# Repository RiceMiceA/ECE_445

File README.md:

# NuChef<sup>TM</sup> - AI Culinary Assistant

## Table of Contents
1. [Final Product](#1-final-product)
    - [Photos](#photos)
    - [YouTube Demo](#youtube-demo)
2. [How to use our repo?](#2-how-to-use-our-repo)
    - [Init](#21-init)
    - [Managing the submodule Unity folder](#22-managing-the-submodule-unity-folder)
    - [Network Configuration](#3-network-configuration)
    - [Troubleshooting](#4-troubleshooting)
5. [Third-Party Libraries & Licenses](#5-third-party-libraries--licenses)

## 1. Final Product
### Photos

### YouTube Demo

## 2. How to use our repo?

### 2.1 Init
#### Freshly Clone 1st time
```bash
git clone --recurse-submodules <repo-url>
```

This does everything:
- clones the parent repo
- initializes submodules
- checks out the correct commits

#### Already cloned repo
```bash
git submodule update --init --recursive
```

### 2.2 Managing the submodule Unity folder
#### 2.2.1 Before Work/Update
#### In parent folder
```bash
git pull
git submodule update --init --recursive
```

#### 2.2.2 Post-work
```bash
cd path/to/submodule
git checkout main
git pull origin main
git add .
git commit -m "Update submodule"
git push origin main

cd /path/to/parent-repo
git add Software/src/Unity-PassthroughCameraApiSamples
git commit -m "Bump submodule"
git push origin main
```

### Verify Health
```bash
git submodule status
```

### Tip
```bash
git config --global submodule.recurse true
# if we wanna track the specific branch
git submodule set-branch --branch tony Software/src/Unity-PassthroughCameraApiSamples
git submodule update --remote
```

## 3. Network Configuration

### Kill previous run
```bash
kill $(lsof -t -i:8000) 
```

### Update IP Address before operation
```bash
Check the current ip address: 
```
When switching networks, update the backend IP (`192.168.x.x`) in these files:

| File                                                                                                                                                                                                                                                                                                       | Line | Variable      |
| ---------------------------------------------------------------------------------------------------------------------------------------------------------------------------------------------------------------------------------------------------------------------------------------------------------- | ---- | ------------- |
| [`Software/src/Unity-PassthroughCameraApiSamples/Assets/PassthroughCameraApiSamples/MultiObjectDetection/DetectionManager/Scripts/BackendClient.cs`](Software/src/Unity-PassthroughCameraApiSamples/Assets/PassthroughCameraApiSamples/MultiObjectDetection/DetectionManager/Scripts/BackendClient.cs#L19) | 19   | `m_baseUrl`   |
| [`Software/src/web_app/main/script.js`](Software/src/web_app/main/script.js#L6)                                                                                                                                                                                                                            | 6    | `BACKEND_URL` |

> **Note:** The ESP32 now communicates via **BLE** (not WiFi), so it no longer needs an IP address or network config.

Then start the backend and BLE bridge:
```bash
# Terminal 1 — backend
cd Software/src/web_app
source .env   # loads OPENAI_API_KEY, OPENAI_MODEL, USE_LLM_PLANNER from .env file
uvicorn backend:app --host 0.0.0.0 --port 8000 --reload

# Terminal 2 — BLE bridge (connects to ESP32 over Bluetooth, forwards to backend)
pip install bleak httpx   # first time only
python ble_bridge.py
```

## 4. Troubleshooting

### Upload new ESP32 file
```bash
~/.platformio/penv/bin/pio run 2>&1 | tail -20
```

### ESP32 BLE not broadcasting / bridge can't find device
1. **Press the physical RESET button** on the ESP32-S3 board. It will re-advertise as `NuChef-Dispenser` within a few seconds.
2. If the bridge still can't find it, kill and restart `ble_bridge.py`. Linux's BlueZ stack sometimes caches stale BLE data.
3. As a last resort, power-cycle the ESP32 (unplug & replug USB).

### Serial port changed (`/dev/ttyACM0` ↔ `/dev/ttyACM1`)
After a reset or replug the port may shift. Check with:
```bash
ls /dev/ttyACM*
```
Then update `upload_port` and `monitor_port` in `Software/src/esp_driver/platformio.ini` if you need to re-flash.

### Permission denied on `/dev/ttyACM*`
```bash
sudo usermod -aG dialout $USER
# then log out & back in (or reboot) for the group to take effect
```

### Bridge connects but dispense doesn't trigger from the UI
- Make sure the backend (`uvicorn`) **and** `ble_bridge.py` are both running.
- Verify `BACKEND_URL` in `script.js` is `window.location.origin` (not a hardcoded IP).
- Check the bridge terminal for `BLE CMD →` and `write OK` logs when you click **Dispense**.

### Quick sanity check (motor spin from CLI)
```bash
# Direct BLE test — bypasses the backend entirely
python3 -c "
import asyncio
from bleak import BleakClient, BleakScanner
SVC  = '4e7a9b1c-d203-4e2a-b8f1-67c1d9e3f5a0'
CMD  = '4e7a9b1c-d203-4e2a-b8f1-67c1d9e3f5a1'
async def test():
    dev = await BleakScanner.find_device_by_name('NuChef-Dispenser', timeout=10)
    async with BleakClient(dev) as c:
        await c.write_gatt_char(CMD, b'spin', response=True)
        await asyncio.sleep(5)
        await c.write_gatt_char(CMD, b'stop', response=True)
asyncio.run(test())
"
```

## 5. Third-Party Libraries & Licenses

### Unity Utility Packages (MIT)
- **Repository:** https://github.com/meta-quest/Unity-UtilityPackages
- **Author:** Meta Platforms, Inc. and affiliates
- **License:** MIT License

> Meta Quest, "Unity-UtilityPackages," GitHub. [Online]. Available: https://github.com/meta-quest/Unity-UtilityPackages. [Accessed: May 7, 2026].

MIT License attribution:
```
Unity Utility Packages
Copyright (c) Meta Platforms, Inc. and affiliates.
Licensed under the MIT License.
https://github.com/meta-quest/Unity-UtilityPackages
```

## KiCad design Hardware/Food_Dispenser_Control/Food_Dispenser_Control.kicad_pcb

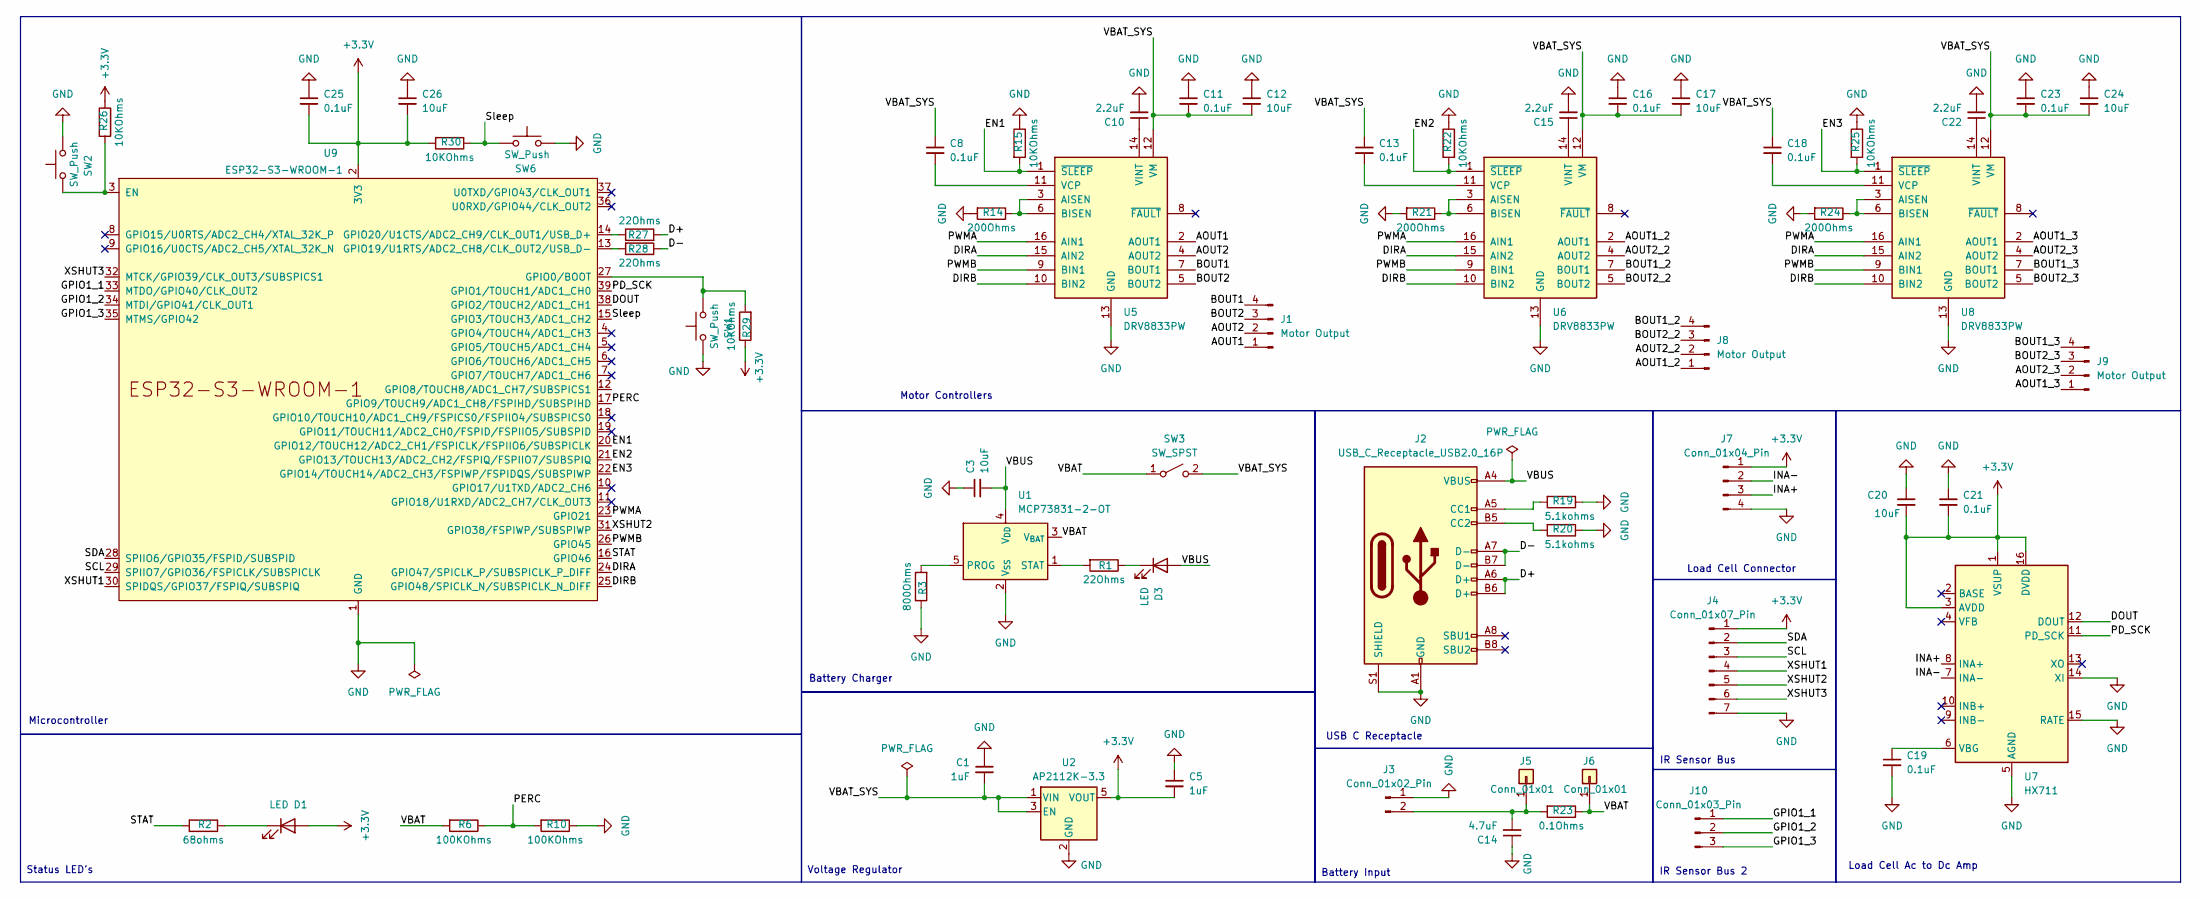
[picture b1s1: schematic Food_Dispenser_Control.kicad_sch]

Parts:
C1, C5: 1uF; C_0805_2012Metric_Pad1.18x1.45mm_HandSolder
C3, C12, C17, C20, C24, C26: 10uF; C_0805_2012Metric_Pad1.18x1.45mm_HandSolder
C8, C11, C13, C16, C18, C19, C21, C23, C25: 0.1uF; C_0805_2012Metric_Pad1.18x1.45mm_HandSolder
C10, C15, C22: 2.2uF; C_0805_2012Metric_Pad1.18x1.45mm_HandSolder
C14: 4.7uF; C_0805_2012Metric_Pad1.18x1.45mm_HandSolder
D1, D3: LED; LED_0805_2012Metric_Pad1.15x1.40mm_HandSolder
J1, J8, J9: Motor Output; TerminalBlock_Phoenix_MKDS-1,5-4_1x04_P5.00mm_Horizontal
J2: USB_C_Receptacle_USB2.0_16P; USB_C_Receptacle_GCT_USB4105-xx-A_16P_TopMnt_Horizontal
J3: Conn_01x02_Pin; TerminalBlock_Phoenix_MKDS-1,5-2_1x02_P5.00mm_Horizontal
J4: Conn_01x07_Pin; TerminalBlock_Phoenix_MKDS-1,5-7_1x07_P5.00mm_Horizontal
J5, J6: Conn_01x01; TestPoint_Pad_D1.5mm
J7: Conn_01x04_Pin; TerminalBlock_Phoenix_MKDS-1,5-4_1x04_P5.00mm_Horizontal
J10: Conn_01x03_Pin; TerminalBlock_Phoenix_MKDS-1,5-3_1x03_P5.00mm_Horizontal
R1, R27, R28: 22Ohms; R_0805_2012Metric_Pad1.20x1.40mm_HandSolder
R2: 68ohms; R_0805_2012Metric_Pad1.20x1.40mm_HandSolder
R3: 800Ohms; R_0805_2012Metric_Pad1.20x1.40mm_HandSolder
R6, R10: 100KOhms; R_0805_2012Metric_Pad1.20x1.40mm_HandSolder
R14, R21, R24: 200Ohms; R_0805_2012Metric_Pad1.20x1.40mm_HandSolder
R15, R22, R25, R26, R29, R30: 10KOhms; R_0805_2012Metric_Pad1.20x1.40mm_HandSolder
R19, R20: 5.1kohms; R_0805_2012Metric_Pad1.20x1.40mm_HandSolder
R23: 0.1Ohms; R_0805_2012Metric_Pad1.20x1.40mm_HandSolder
SW1, SW2, SW6: SW_Push; SW_PUSH_6mm_H5mm
SW3: SW_SPST; SW_DIP_SPSTx01_Slide_6.7x4.1mm_W7.62mm_P2.54mm_LowProfile
U1: MCP73831-2-OT; SOT-23-5
U2: AP2112K-3.3; SOT-23-5
U5, U6, U8: DRV8833PW; TSSOP-16_4.4x5mm_P0.65mm
U7: HX711; SOP-16_3.9x9.9mm_P1.27mm
U9: ESP32-S3-WROOM-1

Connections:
+3.3V: C5.2, C20.2, C21.2, C25.2, C26.2, D1.2 (A), J4.1, J7.1, R26.1, R29.1, R30.2, U2.5 (VOUT), U7.1 (VSUP), U7.3 (AVDD), U7.16 (DVDD), U9.2 (3V3)
/AOUT1: J1.1, U5.2 (AOUT1)
/AOUT1_2: J8.1, U6.2 (AOUT1)
/AOUT1_3: J9.1, U8.2 (AOUT1)
/AOUT2: J1.2, U5.4 (AOUT2)
/AOUT2_2: J8.2, U6.4 (AOUT2)
/AOUT2_3: J9.2, U8.4 (AOUT2)
/BOUT1: J1.4, U5.7 (BOUT1)
/BOUT1_2: J8.4, U6.7 (BOUT1)
/BOUT1_3: J9.4, U8.7 (BOUT1)
/BOUT2: J1.3, U5.5 (BOUT2)
/BOUT2_2: J8.3, U6.5 (BOUT2)
/BOUT2_3: J9.3, U8.5 (BOUT2)
/D+: J2.A6 (D+), J2.B6 (D+), R27.2
/D-: J2.A7 (D-), J2.B7 (D-), R28.1
/DIRA: U5.15 (AIN2), U6.15 (AIN2), U8.15 (AIN2), U9.24 (GPIO47/SPICLK_P/SUBSPICLK_P_DIFF)
/DIRB: U5.10 (BIN2), U6.10 (BIN2), U8.10 (BIN2), U9.25 (GPIO48/SPICLK_N/SUBSPICLK_N_DIFF)
/DOUT: U7.12 (DOUT), U9.38 (GPIO2/TOUCH2/ADC1_CH1)
/EN1: R15.2, U5.1 (~SLEEP), U9.20 (GPIO12/TOUCH12/ADC2_CH1/FSPICLK/FSPIIO6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)
/EN2: R22.2, U6.1 (~SLEEP), U9.21 (GPIO13/TOUCH13/ADC2_CH2/FSPIQ/FSPIIO7/S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)
/EN3: R25.2, U8.1 (~SLEEP), U9.22 (GPIO14/TOUCH14/ADC2_CH3/FSPIWP/FSPIDQS/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)
/GPIO1_1: J10.1, U9.33 (MTDO/GPIO40/CLK_OUT2)
/GPIO1_2: J10.2, U9.34 (MTDI/GPIO41/CLK_OUT1)
/GPIO1_3: J10.3, U9.35 (MTMS/GPIO42)
/INA+: J7.3, U7.8 (INA+)
/INA-: J7.2, U7.7 (INA-)
/PD_SCK: U7.11 (PD_SCK), U9.39 (GPIO1/TOUCH1/ADC1_CH0)
/PERC: R6.1, R10.2, U9.17 (GPIO9/TOUCH9/ADC1_CH8/FSPIHD/SUBSPIHD)
/PWMA: U5.16 (AIN1), U6.16 (AIN1), U8.16 (AIN1), U9.23 (GPIO21)
/PWMB: U5.9 (BIN1), U6.9 (BIN1), U8.9 (BIN1), U9.26 (GPIO45)
/SCL: J4.3, U9.29 (SPIIO7/GPIO36/FSPICLK/SUBSPICLK)
/SDA: J4.2, U9.28 (SPIIO6/GPIO35/FSPID/SUBSPID)
/STAT: R2.2, U9.16 (GPIO46)
/Sleep: R30.1, SW6.1, U9.15 (GPIO3/TOUCH3/ADC1_CH2)
/VBAT: J6.1, R6.2, R23.1, SW3.1 (A), U1.3 (V_{BAT})
/VBAT_SYS: C1.2, C8.1, C11.2, C12.2, C13.1, C16.2, C17.2, C18.1, C23.2, C24.2, SW3.2 (B), U2.1 (VIN), U2.3 (EN), U5.12 (VM), U6.12 (VM), U8.12 (VM)
/VBUS: C3.2, D3.2 (A), J2.A4 (VBUS), J2.A9 (VBUS), J2.B4 (VBUS), J2.B9 (VBUS), U1.4 (V_{DD})
/XSHUT1: J4.4, U9.30 (SPIDQS/GPIO37/FSPIQ/SUBSPIQ)
/XSHUT2: J4.5, U9.31 (GPIO38/FSPIWP/SUBSPIWP)
/XSHUT3: J4.6, U9.32 (MTCK/GPIO39/CLK_OUT3/SUBSPICS1)
GND: C1.1, C3.1, C5.1, C10.2, C11.1, C12.1, C14.1, C15.2, C16.1, C17.1, C19.2, C20.1, C21.1, C22.2, C23.1, C24.1, C25.1, C26.1, J2.A1 (GND), J2.A12 (GND), J2.B1 (GND), J2.B12 (GND), J2.S1 (SHIELD), J3.1, J4.7, J7.4, R3.1, R10.1, R14.2, R15.1, R19.1, R20.1, R21.2, R22.1, R24.2, R25.1, SW1.1, SW2.2, SW6.2, U1.2 (V_{SS}), U2.2 (GND), U5.13 (GND), U6.13 (GND), U7.5 (AGND), U7.14 (XI), U7.15 (RATE), U8.13 (GND), U9.1 (GND), U9.40 (GND), U9.41 (GND)
unnamed: D1.1 (K), R2.1
unnamed: D3.1 (K), R1.1
unnamed: J2.A5 (CC1), R19.2
unnamed: J2.B5 (CC2), R20.2
unnamed: C14.2, J3.2, J5.1, R23.2
unnamed: R3.2, U1.5 (PROG)
unnamed: R1.2, U1.1 (STAT)
unnamed: R14.1, U5.3 (AISEN), U5.6 (BISEN)
unnamed: C8.2, U5.11 (VCP)
unnamed: C10.1, U5.14 (VINT)
unnamed: R21.1, U6.3 (AISEN), U6.6 (BISEN)
unnamed: C13.2, U6.11 (VCP)
unnamed: C15.1, U6.14 (VINT)
unnamed: C19.1, U7.6 (VBG)
unnamed: R24.1, U8.3 (AISEN), U8.6 (BISEN)
unnamed: C18.2, U8.11 (VCP)
unnamed: C22.1, U8.14 (VINT)
unnamed: R26.2, SW2.1, U9.3 (EN)
unnamed: R29.2, SW1.2, U9.27 (GPIO0/BOOT)
unnamed: R28.2, U9.13 (GPIO19/U1RTS/ADC2_CH8/CLK_OUT2/USB_D-)
unnamed: R27.1, U9.14 (GPIO20/U1CTS/ADC2_CH9/CLK_OUT1/USB_D+)

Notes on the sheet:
IR Sensor Bus 2
Status LED's
IR Sensor Bus
Load Cell Connector
Motor Controllers
Microcontroller
Battery Input
Battery Charger
USB C Receptacle
Load Cell Ac to Dc Amp
Voltage Regulator

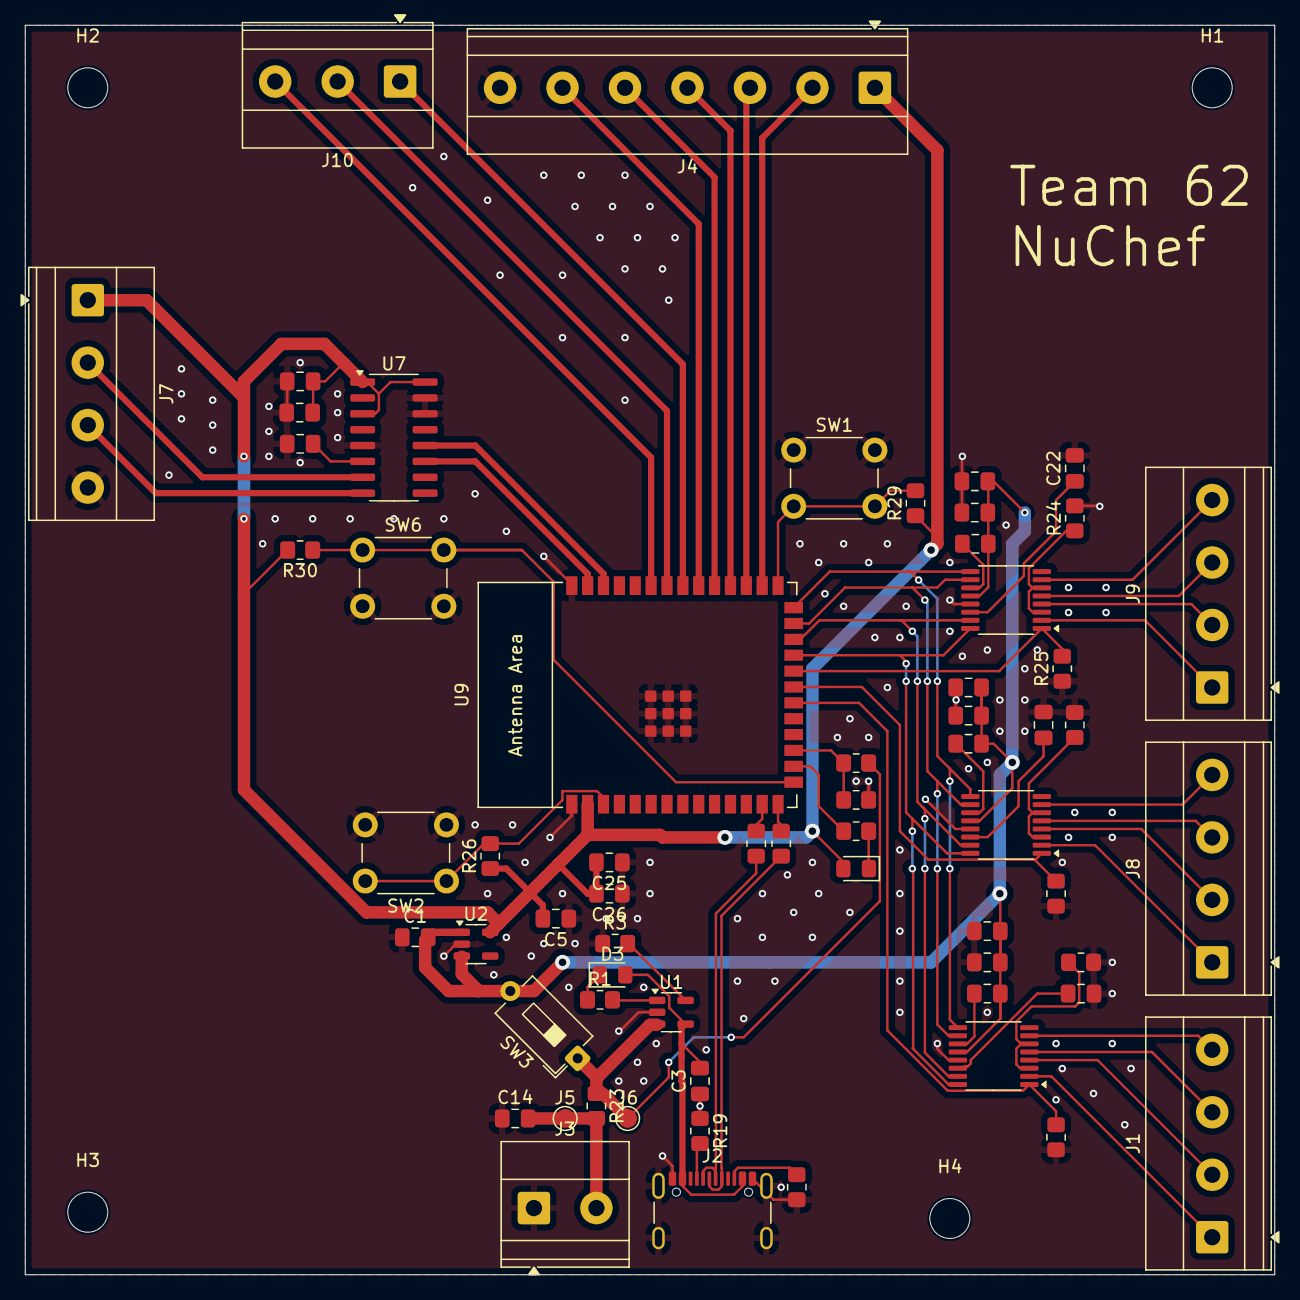
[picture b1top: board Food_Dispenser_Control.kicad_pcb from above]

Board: 2 copper layers, 100.0 x 100.0 mm, 67 parts (0 on the bottom side), 62 nets.

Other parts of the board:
H1, H2, H3, H4: MountingHole; MountingHole_3.2mm_M3

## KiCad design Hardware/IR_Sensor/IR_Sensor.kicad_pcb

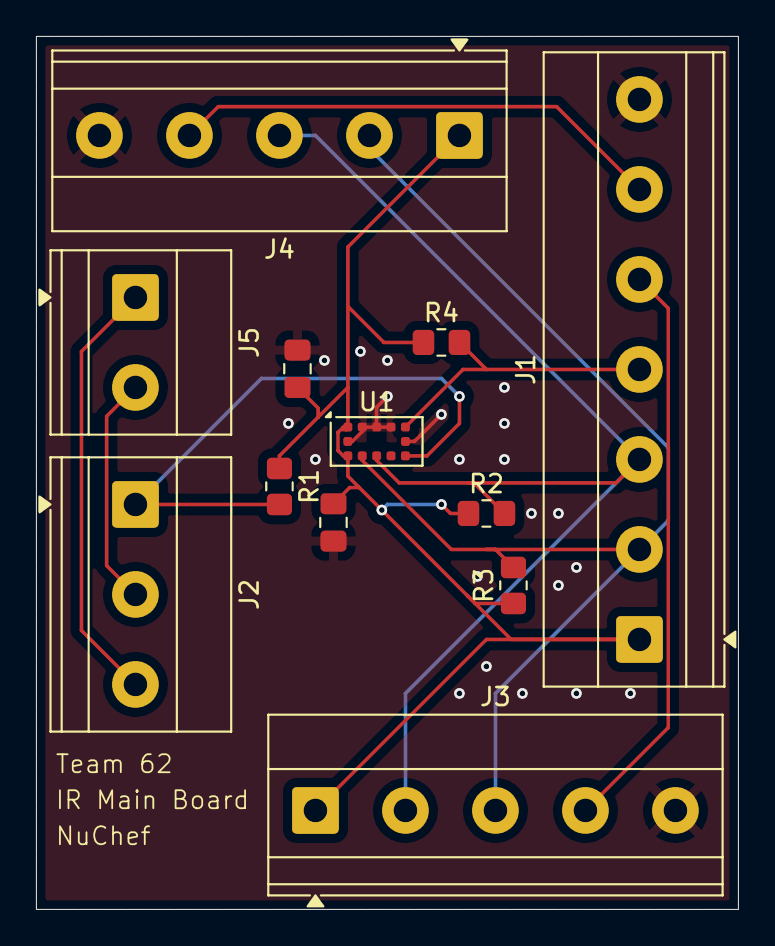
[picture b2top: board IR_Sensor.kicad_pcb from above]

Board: 2 copper layers, 39.0 x 48.5 mm, 12 parts (0 on the bottom side), 10 nets.

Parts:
C1: 100nF; C_0805_2012Metric_Pad1.18x1.45mm_HandSolder
C2: 4.7uF; C_0805_2012Metric_Pad1.18x1.45mm_HandSolder
J1: Conn_01x07_Pin; TerminalBlock_Phoenix_MKDS-1,5-7_1x07_P5.00mm_Horizontal
J2: Conn_01x03_Pin; TerminalBlock_Phoenix_MKDS-1,5-3_1x03_P5.00mm_Horizontal
J3, J4: Conn_01x05_Pin; TerminalBlock_Phoenix_MKDS-1,5-5_1x05_P5.00mm_Horizontal
J5: Conn_01x02_Pin; TerminalBlock_Phoenix_MKDS-1,5-2_1x02_P5.00mm_Horizontal
R1, R2, R3, R4: 4.7k; R_0805_2012Metric_Pad1.20x1.40mm_HandSolder
U1: VL53L0CXV0DH1; ST_VL53L1x

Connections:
+3.3V: C1.1, C2.1, J1.1, J3.1, J4.1, R1.1, R2.1, R3.1, R4.1, U1.1 (AVDDVCSEL), U1.11 (AVDD)
/GPIO1_1: J2.1, R1.2, U1.7 (GPIO1)
/GPIO1_2: J2.2, J5.2
/GPIO1_3: J2.3, J5.1
/SCL: J1.2, J3.3, J4.2, R3.2, U1.10 (SCL)
/SDA: J1.3, J3.2, J4.3, R2.2, U1.9 (SDA)
/XSHUT1: J1.4, R4.2, U1.5 (XSHUT)
/XSHUT2: J1.5, J3.4
/XSHUT3: J1.6, J4.4
GND: C1.2, C2.2, J1.7, J3.5, J4.5, U1.2 (AVSSVCSEL), U1.3 (GND), U1.4 (GND), U1.6 (GND), U1.12 (GND)

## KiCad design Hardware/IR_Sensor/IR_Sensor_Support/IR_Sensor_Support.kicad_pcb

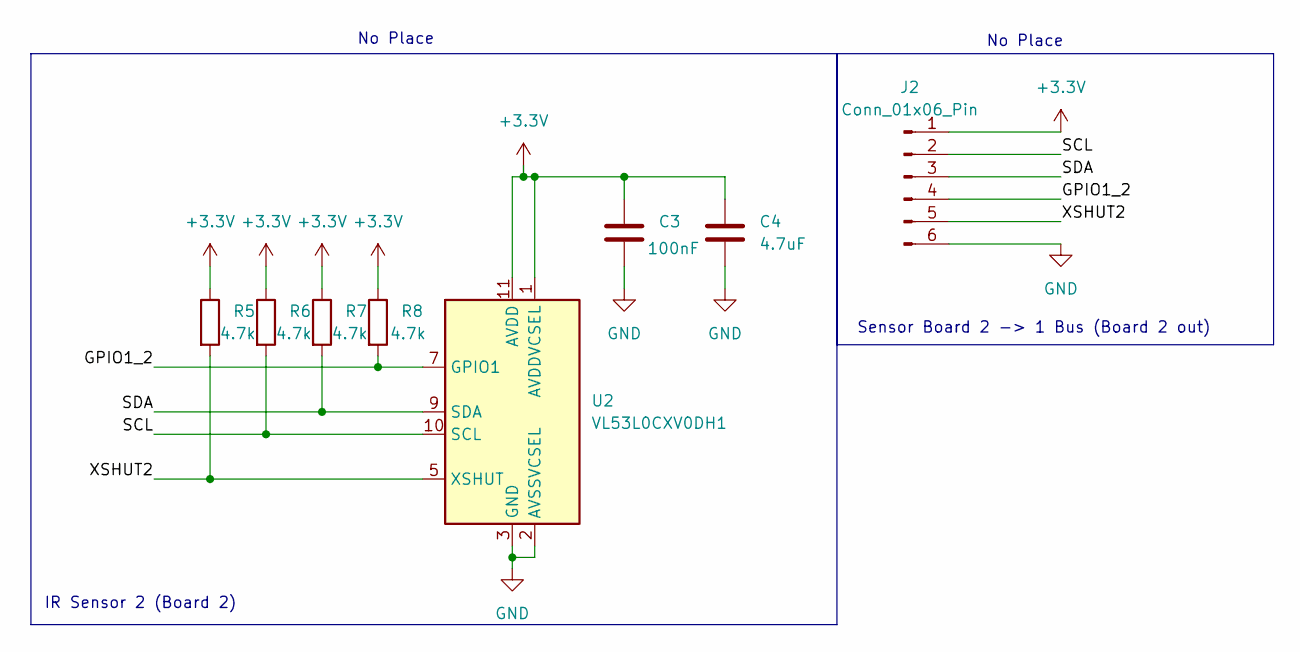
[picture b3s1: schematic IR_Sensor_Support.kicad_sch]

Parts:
C3: 100nF; C_0805_2012Metric
C4: 4.7uF; C_0805_2012Metric
J2: Conn_01x06_Pin; TerminalBlock_Phoenix_MKDS-1,5-6_1x06_P5.00mm_Horizontal
R5, R6, R7, R8: 4.7k; R_0805_2012Metric
U2: VL53L0CXV0DH1; ST_VL53L1x

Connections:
+3.3V: C3.1, C4.1, J2.1, R5.1, R6.1, R7.1, R8.1, U2.1 (AVDDVCSEL), U2.11 (AVDD)
/GPIO1_2: J2.4, R8.2, U2.7 (GPIO1)
/SCL: J2.2, R6.2, U2.10 (SCL)
/SDA: J2.3, R7.2, U2.9 (SDA)
/XSHUT2: J2.5, R5.2, U2.5 (XSHUT)
GND: C3.2, C4.2, J2.6, U2.2 (AVSSVCSEL), U2.3 (GND), U2.4 (GND), U2.6 (GND), U2.12 (GND)

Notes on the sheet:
No Place
Sensor Board 2 -> 1 Bus (Board 2 out)
IR Sensor 2 (Board 2)

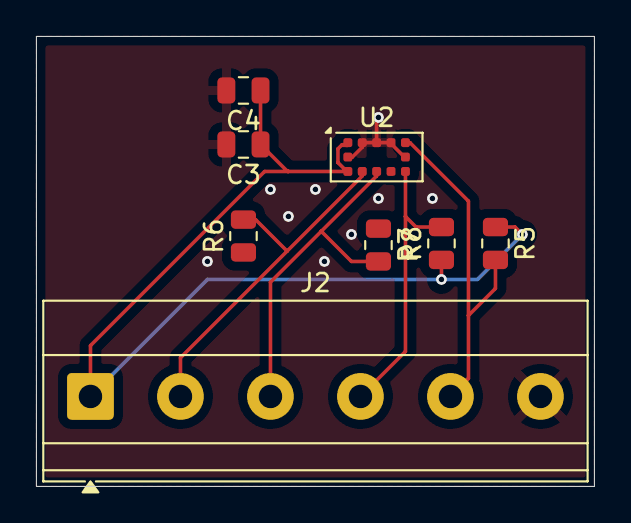
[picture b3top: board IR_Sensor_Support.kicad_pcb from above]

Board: 2 copper layers, 31.0 x 25.0 mm, 8 parts (0 on the bottom side), 6 nets.

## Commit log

2026-02-24 Tony init the workspace
2026-02-25 Da Board
2026-02-25 IR sensor board
2026-02-25 s3 migration
2026-02-26 schematic and footprints
2026-02-28 Some stuff idk
2026-03-01 Tony software doc
2026-03-03 Layout
2026-03-03 Routing
2026-03-03 Ground Plane
2026-03-03 Ground routing
2026-03-04 adding web app code
2026-03-04 IR Main Board
2026-03-08 Motor driver code, 1st draft, breadboard demo
2026-03-10 Added WiFi Capabilities to comm w/ the ESP32
2026-03-24 Add Unity-PassthroughCameraApiSamples as submodule
2026-03-24 Submodule tracking tony branch as well
2026-03-29 backend construction
2026-03-30 Bump submodule
2026-03-30 Quest-Unity pipeline works
2026-03-30 Proper integrate into this repo with Unity work
2026-03-31 EOD checkpoint
2026-04-05 Restrained LLM working at Triangle
2026-04-06 Motor Integration Successful
2026-04-06 load cell functioning on serial monitor
2026-04-13 Added notebooks folder
2026-04-15 updated hardware
2026-04-21 Progress Demo
2026-04-21 Apr.21st testing on PCB
2026-04-25 Testing IR Sensors
2026-04-26 Ingredient Highlighten Animation
2026-04-26 Backup 04/26 3:44PM
2026-04-26 Demo ready state
2026-04-26 Update Lab Notebook
2026-04-27 Ingredient Weight Measurements Included
2026-04-27 User Experience Ready Except for Prefabs
2026-04-27 School Wifi Works
2026-04-27 27th Demo Backup
2026-04-27 Duplicates in measurement
2026-04-27 Demo ready except for better Mesh
2026-05-06 FINAL
2026-05-07 Renamed Notebook and Organized Materials
2026-05-07 Griffin & Jackson ready for updating notebook
2026-05-08 Notebook Ready
2026-05-08 Tony finished polishing notebook
2026-05-08 All images in Notebook folder
2026-05-08 Tony adding proper license
2026-05-08 Use .env for API key instead of hardcoded export
2026-05-08 Rename Screenshot 2026-05-07 220225.png to microcontroller_v1
2026-05-08 Rename Screenshot 2026-05-07 220428.png to voltage_reg_V1
2026-05-08 Rename Screenshot 2026-05-07 220447.png to USBC_V1
2026-05-08 Rename Screenshot 2026-05-07 222739.png to schematic
2026-05-08 Rename Screenshot 2026-05-07 223323.png to Routing
2026-05-08 Rename Screenshot 2026-05-07 233020.png to Spice Container
2026-05-08 Rename Battery Perf.png to Battery_Perf.png
2026-05-08 Rename Routing to Routing.png
2026-05-08 Rename schematic to schematic.png
2026-05-08 jcb10 notebook completed
